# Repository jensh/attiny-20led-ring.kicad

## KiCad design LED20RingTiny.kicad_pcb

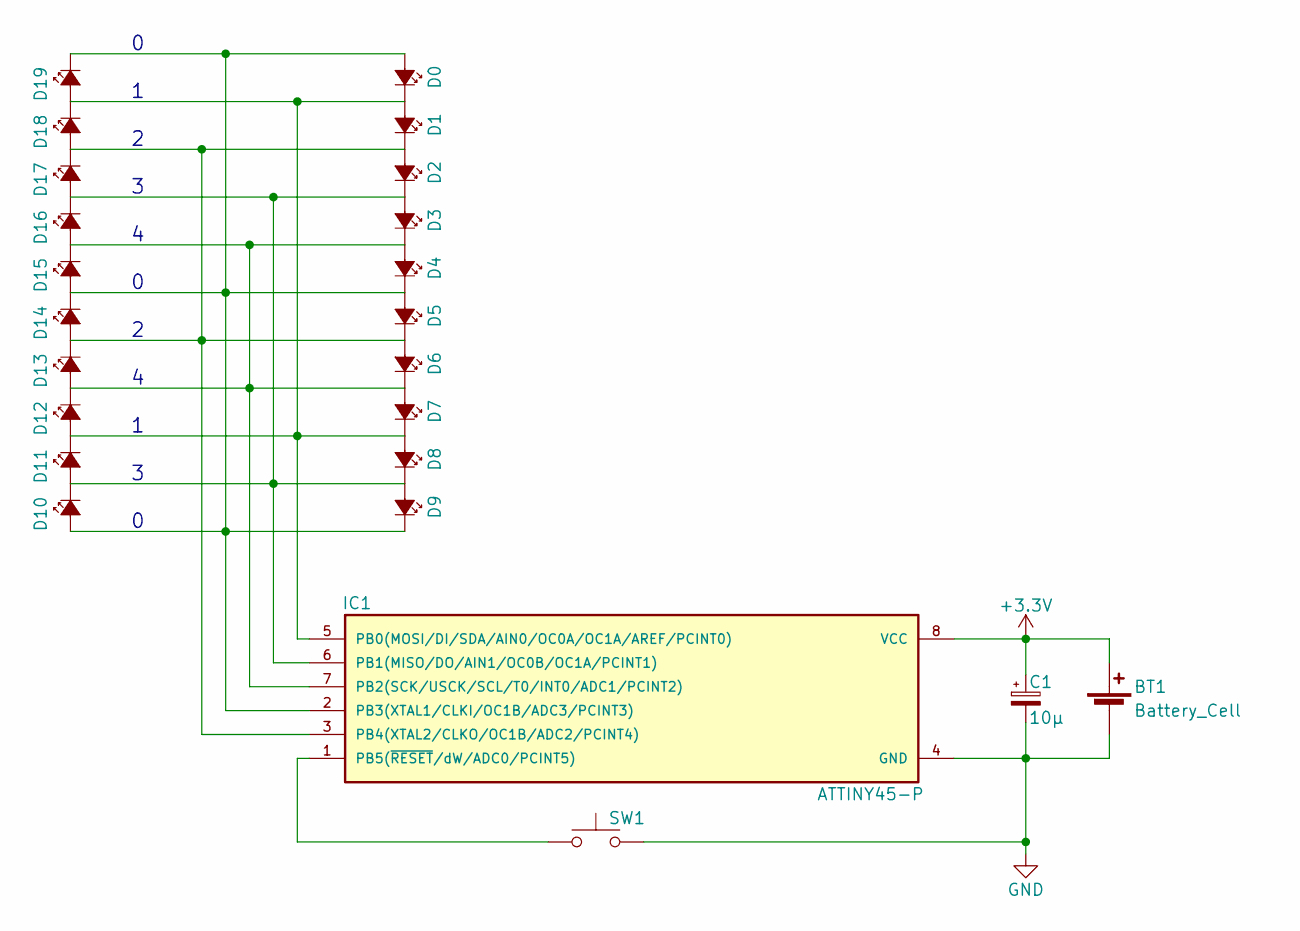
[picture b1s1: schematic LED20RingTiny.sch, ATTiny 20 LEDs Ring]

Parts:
BT1: Battery_Cell; CR2032V
C1: 10µ; SMD-1206_Pol
D0, D1, D2, D3, D4, D5, D6, D7, D8, D9, D10, D11, D12, D13, D14, D15, D16, D17, D18, D19: LED; LED_0805
IC1: ATTINY45-P; SOIJ-8_5.3x5.3mm_Pitch1.27mm
SW1: SW_Push; SW_SPST_KMR2

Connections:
+3V3: BT1.1 (+), C1.1, IC1.8 (VCC)
GND: BT1.2 (-), C1.2, IC1.4 (GND), SW1.2
unnamed: D0.1 (K), D1.2 (A), D7.1 (K), D8.2 (A), D11.1 (K), D12.2 (A), D18.1 (K), D19.2 (A), IC1.5 (PB0(MOSI/DI/SDA/AIN0/OC0A/OC1A/AREF/PCI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)
unnamed: D0.2 (A), D4.1 (K), D5.2 (A), D9.1 (K), D10.2 (A), D14.1 (K), D15.2 (A), D19.1 (K), IC1.2 (PB3(XTAL1/CLKI/OC1B/ADC3/PCINT3))
unnamed: D1.1 (K), D2.2 (A), D5.1 (K), D6.2 (A), D13.1 (K), D14.2 (A), D17.1 (K), D18.2 (A), IC1.3 (PB4(XTAL2/CLKO/OC1B/ADC2/PCINT4))
unnamed: D2.1 (K), D3.2 (A), D8.1 (K), D9.2 (A), D10.1 (K), D11.2 (A), D16.1 (K), D17.2 (A), IC1.6 (PB1(MISO/DO/AIN1/OC0B/OC1A/PCINT1))
unnamed: D3.1 (K), D4.2 (A), D6.1 (K), D7.2 (A), D12.1 (K), D13.2 (A), D15.1 (K), D16.2 (A), IC1.7 (PB2(SCK/USCK/SCL/T0/INT0/ADC1/PCINT2))
unnamed: IC1.1 (PB5(~RESET~/dW/ADC0/PCINT5)), SW1.1

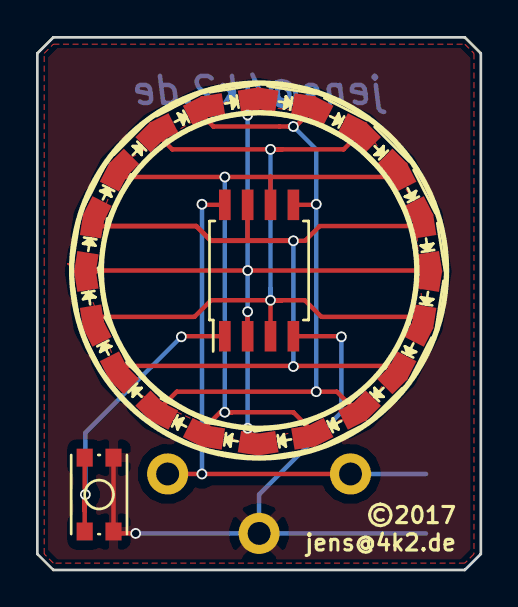
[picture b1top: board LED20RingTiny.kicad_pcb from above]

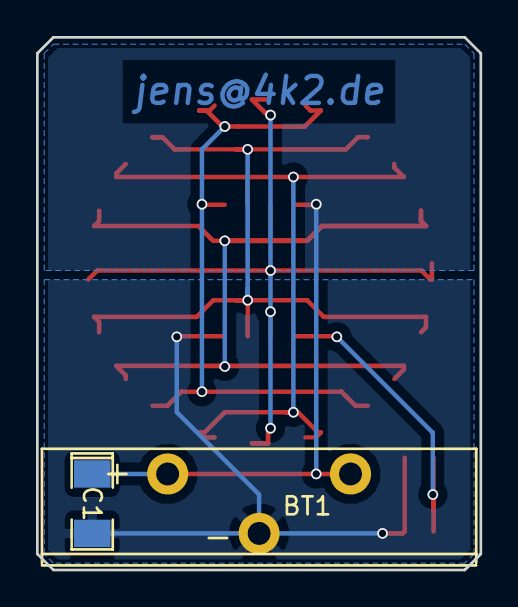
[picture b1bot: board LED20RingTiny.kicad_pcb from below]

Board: 2 copper layers, 24.6 x 29.6 mm, 24 parts (2 on the bottom side), 8 nets.

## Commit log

2017-03-29 Initial commit.
2017-03-29 Align LEDs on 5mils grid
2017-03-29 Add some Traces
2017-03-31 Exact LED locations on circle.
2017-03-31 Improve
2017-03-31 Cleanups
2017-03-31 Add cache : EESchema-LIBRARY
2017-04-01 Add Meta data: Date, name, company
2017-04-01 Inc (c)2017, jens@4k2.de text to 0.9mm
2017-04-01 Gerber files
2017-04-02 Panelized version
2017-04-03 Add Edge Cuts
2017-04-03 Recalc polygones
2017-12-28 Add pcb and schema images.
2017-12-28 Title text in schema

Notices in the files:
LED20RingTiny.kicad_pcb:
©2017
